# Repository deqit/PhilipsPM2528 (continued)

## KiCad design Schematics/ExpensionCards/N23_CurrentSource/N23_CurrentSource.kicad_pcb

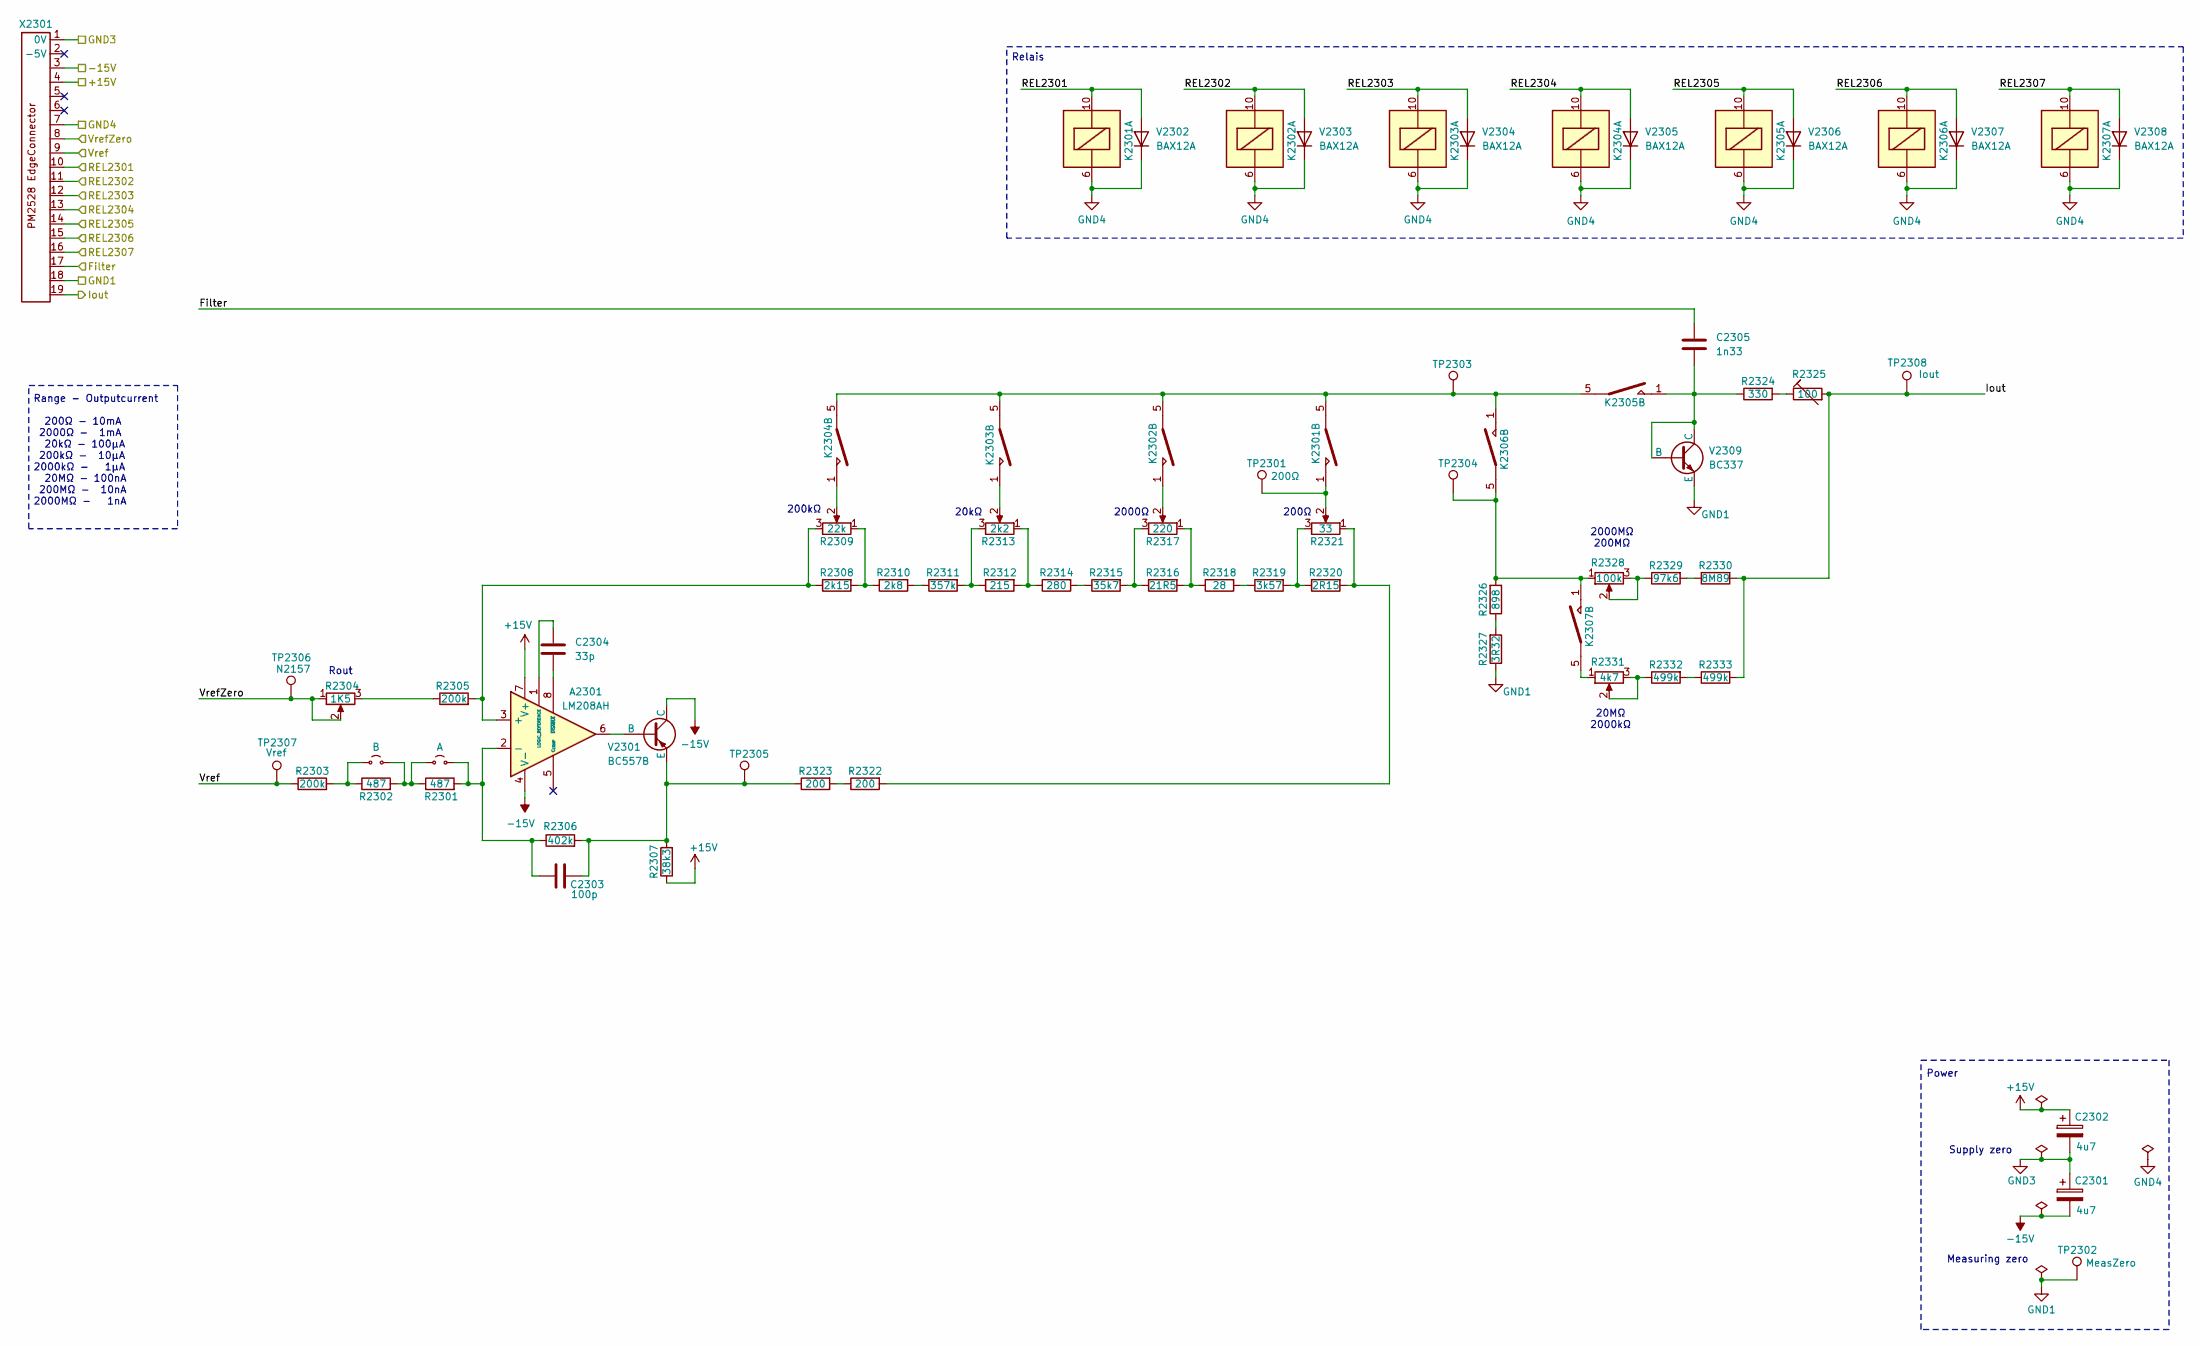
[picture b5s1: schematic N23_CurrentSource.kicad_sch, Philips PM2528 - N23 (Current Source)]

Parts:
A2301: LM208AH; TO-99-8
C2301, C2302: 4u7; CP_Radial_Tantal_D4.5mm_P5.00mm
C2303: 100p; C_Disc_D4.3mm_W1.9mm_P5.00mm
C2304: 33p; C_Disc_D4.3mm_W1.9mm_P5.00mm
C2305: 1n33; C_Axial_L5.1mm_D3.1mm_P15.00mm_Horizontal
JP2301: B; TestPoint_Bridge_Pitch5.08mm_Drill0.7mm
JP2302: A; TestPoint_Bridge_Pitch5.08mm_Drill0.7mm
K2301, K2302, K2303, K2304, K2305, K2306, K2307: Reed relay assy
R2301: 487; R_Axial_DIN0309_L9.0mm_D3.2mm_P12.70mm_Horizontal
R2302: 487; R_Axial_DIN0207_L6.3mm_D2.5mm_P10.16mm_Horizontal
R2303: 200k; R_Axial_DIN0207_L6.3mm_D2.5mm_P10.16mm_Horizontal
R2304: 1K5; Trimmer vertical
R2305: 200k; R_Axial_DIN0309_L9.0mm_D3.2mm_P12.70mm_Horizontal
R2306: 402k; R_Axial_DIN0309_L9.0mm_D3.2mm_P12.70mm_Horizontal
R2307: 38k3; R_Axial_DIN0207_L6.3mm_D2.5mm_P10.16mm_Horizontal
R2308: 2k15; R_Axial_DIN0207_L6.3mm_D2.5mm_P10.16mm_Horizontal
R2309: 22k; Trimmer vertical
R2310: 2k8; R_Axial_DIN0207_L6.3mm_D2.5mm_P10.16mm_Horizontal
R2311: 357k; R_Axial_DIN0309_L9.0mm_D3.2mm_P12.70mm_Horizontal
R2312: 215; R_Axial_DIN0207_L6.3mm_D2.5mm_P10.16mm_Horizontal
R2313: 2k2; Trimmer vertical
R2314: 280; R_Axial_DIN0207_L6.3mm_D2.5mm_P10.16mm_Horizontal
R2315: 35k7; R_Axial_DIN0207_L6.3mm_D2.5mm_P10.16mm_Horizontal
R2316: 21R5; R_Axial_DIN0207_L6.3mm_D2.5mm_P10.16mm_Horizontal
R2317: 220; Trimmer vertical
R2318: 28; R_Axial_DIN0207_L6.3mm_D2.5mm_P10.16mm_Horizontal
R2319: 3k57; R_Axial_DIN0207_L6.3mm_D2.5mm_P10.16mm_Horizontal
R2320: 2R15; R_Axial_DIN0207_L6.3mm_D2.5mm_P10.16mm_Horizontal
R2321: 33; Trimmer vertical
R2322, R2323: 200; R_Axial_DIN0309_L9.0mm_D3.2mm_P12.70mm_Horizontal
R2324: 330; R_Axial_DIN0614_L14.3mm_D5.7mm_P25.40mm_Horizontal
R2325: 100; RV_Disc_D7mm_W3.9mm_P5mm
R2326: 898; R_Axial_DIN0207_L6.3mm_D2.5mm_P10.16mm_Horizontal
R2327: 3R32; R_Axial_DIN0207_L6.3mm_D2.5mm_P10.16mm_Horizontal
R2328: 100k; Trimmer vertical
R2329: 97k6; R_Axial_DIN0207_L6.3mm_D2.5mm_P10.16mm_Horizontal
R2330: 8M89; R_Axial_DIN0411_L9.9mm_D3.6mm_P15.24mm_Horizontal
R2331: 4k7; Trimmer vertical
R2332, R2333: 499k; R_Axial_DIN0309_L9.0mm_D3.2mm_P12.70mm_Horizontal
TP2301: 200Ω; Pin_D0.9mm_L10.0mm_W2.4mm_FlatFork
TP2302: MeasZero; Pin_D0.9mm_L10.0mm_W2.4mm_FlatFork
TP2303, TP2304, TP2305: Pin_D0.9mm_L10.0mm_W2.4mm_FlatFork
TP2306: N2157; Pin_D0.9mm_L10.0mm_W2.4mm_FlatFork
TP2307: Vref; Pin_D0.9mm_L10.0mm_W2.4mm_FlatFork
TP2308: Iout; Pin_D0.9mm_L10.0mm_W2.4mm_FlatFork
V2301: BC557B; TO-92
V2302, V2303, V2304, V2305, V2306, V2307, V2308: BAX12A; D_DO-41_SOD81_P10.16mm_Horizontal
V2309: BC337; TO-92
X2301: PM2528_RiserCardConnector

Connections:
+15V: A2301.7 (V+), C2302.1, R2307.1, X2301.4
-15V: A2301.4 (V-), C2301.2, V2301.1 (C), X2301.3
/Filter: C2305.2, X2301.17
/Iout: R2325.2, R2330.2, R2333.2, TP2308.1, X2301.19
/REL2301: K2301.10, V2302.2 (A), X2301.10
/REL2302: K2302.10, V2303.2 (A), X2301.11
/REL2303: K2303.10, V2304.2 (A), X2301.12
/REL2304: K2304.10, V2305.2 (A), X2301.13
/REL2305: K2305.10, V2306.2 (A), X2301.14
/REL2306: K2306.10, V2307.2 (A), X2301.15
/REL2307: K2307.10, V2308.2 (A), X2301.16
/Vref: R2303.1, TP2307.1, X2301.9
/VrefZero: R2304.1, R2304.2, TP2306.1, X2301.8
GND1: R2327.1, TP2302.1, V2309.3 (E), X2301.18
GND3: C2301.1, C2302.2, X2301.1 (0V)
GND4: K2301.6, K2302.6, K2303.6, K2304.6, K2305.6, K2306.6, K2307.6, V2302.1 (K), V2303.1 (K), V2304.1 (K), V2305.1 (K), V2306.1 (K), V2307.1 (K), V2308.1 (K), X2301.7
unnamed: A2301.3 (+), R2305.2, R2308.1, R2309.3
unnamed: A2301.2 (-), C2303.2, JP2302.2 (B), R2301.2, R2306.1
unnamed: A2301.1 (LOGIC_REFERENCE), C2304.1
unnamed: A2301.8 (~DISABLE), C2304.2
unnamed: JP2301.1 (A), R2302.1, R2303.2
unnamed: JP2301.2 (B), JP2302.1 (A), R2301.1, R2302.2
unnamed: K2301.1, R2321.2, TP2301.1
unnamed: K2301.5, K2302.5, K2303.5, K2304.5, K2305.5, K2306.1, TP2303.1
unnamed: K2302.1, R2317.2
unnamed: K2303.1, R2313.2
unnamed: K2304.1, R2309.2
unnamed: K2306.5, K2307.1, R2326.2, R2328.1, TP2304.1
unnamed: K2307.5, R2331.1
unnamed: R2304.3, R2305.1
unnamed: R2308.2, R2309.1, R2310.1
unnamed: R2310.2, R2311.1
unnamed: R2311.2, R2312.1, R2313.3
unnamed: R2312.2, R2313.1, R2314.1
unnamed: R2314.2, R2315.1
unnamed: R2315.2, R2316.1, R2317.3
unnamed: R2316.2, R2317.1, R2318.1
unnamed: R2318.2, R2319.1
unnamed: R2319.2, R2320.1, R2321.3
unnamed: R2320.2, R2321.1, R2322.2
unnamed: R2322.1, R2323.2
unnamed: R2324.2, R2325.1
unnamed: R2326.1, R2327.2
unnamed: R2328.2, R2328.3, R2329.1
unnamed: R2329.2, R2330.1
unnamed: R2331.2, R2331.3, R2332.1
unnamed: R2332.2, R2333.1
unnamed: A2301.6, V2301.2 (B)
unnamed: C2303.1, R2306.2, R2307.2, R2323.1, TP2305.1, V2301.3 (E)
unnamed: C2305.1, K2305.1, R2324.1, V2309.1 (C), V2309.2 (B)

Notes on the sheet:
200Ω
Power
Measuring zero
20kΩ
2000MΩ 200MΩ
200kΩ
20MΩ 2000kΩ
Relais
2000Ω
Rout
Range - Outputcurrent 200Ω - 10mA 2000Ω - 1mA 20kΩ - 100µA 200kΩ - 10µA 2000kΩ - 1µA 20MΩ - 100nA 200MΩ - 10nA 2000MΩ - 1nA
Supply zero

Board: 2 copper layers, 66 parts (0 on the bottom side), 50 nets, no tracks yet.

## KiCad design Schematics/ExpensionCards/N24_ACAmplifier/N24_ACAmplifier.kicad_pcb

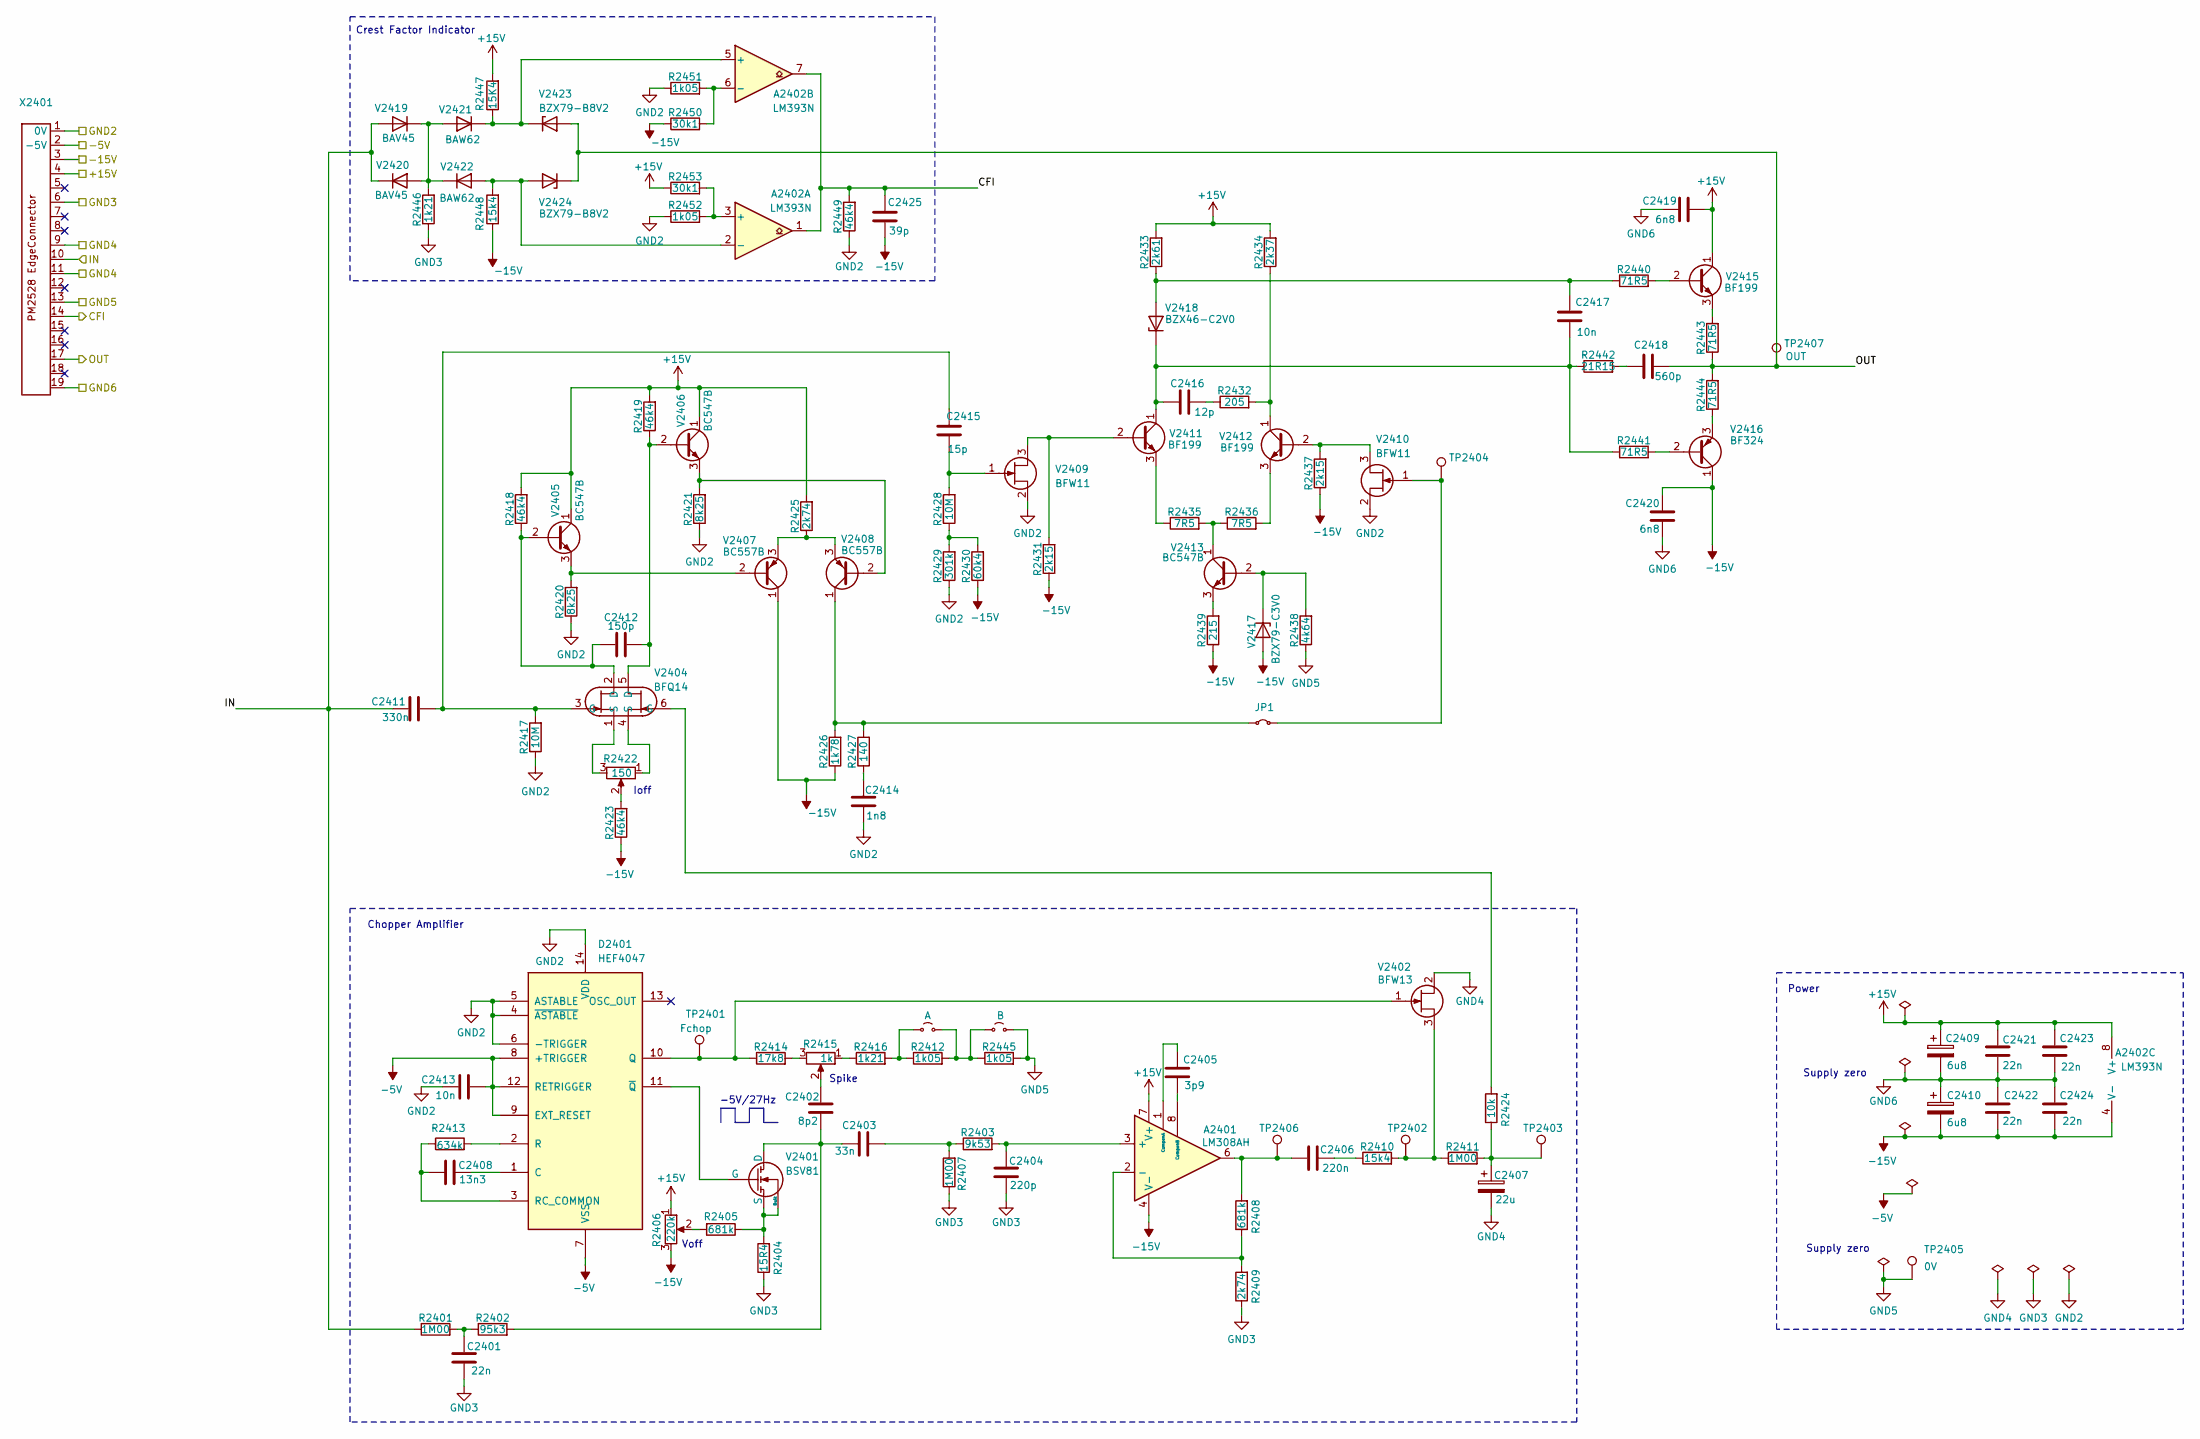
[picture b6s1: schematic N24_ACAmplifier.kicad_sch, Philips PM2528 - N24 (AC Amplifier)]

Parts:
A2401: LM308AH; DIP-8_W7.62mm
A2402: LM393N; DIP-8_W7.62mm
C2401: 22n; C_Rect_L13.0mm_W4.0mm_P10.00mm_FKS3_FKP3_MKS4
C2402: 8p2; C_Disc_D4.3mm_W1.9mm_P5.00mm
C2403: 33n; C_Rect_L13.0mm_W4.0mm_P10.00mm_FKS3_FKP3_MKS4
C2404: 220p; C_Disc_D4.3mm_W1.9mm_P5.00mm
C2405: 3p9; C_Disc_D4.3mm_W1.9mm_P5.00mm
C2406: 220n; C_Rect_L13.0mm_W4.0mm_P10.00mm_FKS3_FKP3_MKS4
C2407: 22u; CP_Radial_Tantal_D4.5mm_P5.00mm
C2408: 13n3; C_Axial_L5.1mm_D3.1mm_P15.00mm_Horizontal
C2409, C2410: 6u8; CP_Radial_Tantal_D4.5mm_P5.00mm
C2411: 330n; C_Rect_L18.0mm_W5.0mm_P15.00mm_FKS3_FKP3
C2412: 150p; C_Disc_D4.3mm_W1.9mm_P5.00mm
C2413, C2417: 10n; C_Disc_D4.3mm_W1.9mm_P5.00mm
C2414: 1n8; C_Disc_D4.3mm_W1.9mm_P5.00mm
C2415: 15p; C_Disc_D4.3mm_W1.9mm_P5.00mm
C2416: 12p; C_Disc_D4.3mm_W1.9mm_P5.00mm
C2418: 560p; C_Disc_D4.3mm_W1.9mm_P5.00mm
C2419, C2420: 6n8; C_Disc_D4.3mm_W1.9mm_P5.00mm
C2421, C2422, C2423, C2424: 22n; C_Disc_D4.3mm_W1.9mm_P5.00mm
C2425: 39p; C_Disc_D4.3mm_W1.9mm_P5.00mm
D2401: HEF4047; DIP-14_W7.62mm
JP1: Jumper_2_Small_Bridged; TestPoint_Bridge_Pitch5.08mm_Drill0.7mm
JP2401: A; TestPoint_Bridge_Pitch5.08mm_Drill0.7mm
JP2402: B; TestPoint_Bridge_Pitch5.08mm_Drill0.7mm
R2401, R2407, R2411: 1M00; R_Axial_DIN0207_L6.3mm_D2.5mm_P10.16mm_Horizontal
R2402: 95k3; R_Axial_DIN0207_L6.3mm_D2.5mm_P10.16mm_Horizontal
R2403: 9k53; R_Axial_DIN0207_L6.3mm_D2.5mm_P10.16mm_Horizontal
R2404: 15R4; R_Axial_DIN0207_L6.3mm_D2.5mm_P10.16mm_Horizontal
R2405, R2408: 681k; R_Axial_DIN0207_L6.3mm_D2.5mm_P10.16mm_Horizontal
R2406: 220k; Trimmer vertical
R2409, R2425: 2k74; R_Axial_DIN0207_L6.3mm_D2.5mm_P10.16mm_Horizontal
R2410, R2448: 15k4; R_Axial_DIN0207_L6.3mm_D2.5mm_P10.16mm_Horizontal
R2412, R2445, R2451, R2452: 1k05; R_Axial_DIN0207_L6.3mm_D2.5mm_P10.16mm_Horizontal
R2413: 634k; R_Axial_DIN0207_L6.3mm_D2.5mm_P10.16mm_Horizontal
R2414: 17k8; R_Axial_DIN0207_L6.3mm_D2.5mm_P10.16mm_Horizontal
R2415: 1k; Trimmer vertical
R2416, R2446: 1k21; R_Axial_DIN0207_L6.3mm_D2.5mm_P10.16mm_Horizontal
R2417, R2428: 10M; R_Axial_DIN0207_L6.3mm_D2.5mm_P10.16mm_Horizontal
R2418, R2419, R2423, R2449: 46k4; R_Axial_DIN0207_L6.3mm_D2.5mm_P10.16mm_Horizontal
R2420, R2421: 8k25; R_Axial_DIN0207_L6.3mm_D2.5mm_P10.16mm_Horizontal
R2422: 150; Trimmer vertical
R2424: 10k; R_Axial_DIN0207_L6.3mm_D2.5mm_P10.16mm_Horizontal
R2426: 1k78; R_Axial_DIN0207_L6.3mm_D2.5mm_P10.16mm_Horizontal
R2427: 140; R_Axial_DIN0207_L6.3mm_D2.5mm_P10.16mm_Horizontal
R2429: 301k; R_Axial_DIN0207_L6.3mm_D2.5mm_P10.16mm_Horizontal
R2430: 60k4; R_Axial_DIN0207_L6.3mm_D2.5mm_P10.16mm_Horizontal
R2431, R2437: 2k15; R_Axial_DIN0207_L6.3mm_D2.5mm_P10.16mm_Horizontal
R2432: 205; R_Axial_DIN0207_L6.3mm_D2.5mm_P10.16mm_Horizontal
R2433: 2k61; R_Axial_DIN0207_L6.3mm_D2.5mm_P10.16mm_Horizontal
R2434: 2k37; R_Axial_DIN0207_L6.3mm_D2.5mm_P10.16mm_Horizontal
R2435, R2436: 7R5; R_Axial_DIN0207_L6.3mm_D2.5mm_P10.16mm_Horizontal
R2438: 4k64; R_Axial_DIN0207_L6.3mm_D2.5mm_P10.16mm_Horizontal
R2439: 215; R_Axial_DIN0207_L6.3mm_D2.5mm_P10.16mm_Horizontal
R2440, R2441, R2443, R2444: 71R5; R_Axial_DIN0207_L6.3mm_D2.5mm_P10.16mm_Horizontal
R2442: 21R15; R_Axial_DIN0207_L6.3mm_D2.5mm_P10.16mm_Horizontal
R2447: 15K4; R_Axial_DIN0207_L6.3mm_D2.5mm_P10.16mm_Horizontal
R2450, R2453: 30k1; R_Axial_DIN0207_L6.3mm_D2.5mm_P10.16mm_Horizontal
TP2401: Fchop; Pin_D0.9mm_L10.0mm_W2.4mm_FlatFork
TP2402, TP2403: Pin_D0.9mm_L10.0mm_W2.4mm_FlatFork
TP2404: something; Pin_D0.9mm_L10.0mm_W2.4mm_FlatFork
TP2405: 0V; Pin_D0.9mm_L10.0mm_W2.4mm_FlatFork
TP2406: AC_RMS?; Pin_D0.9mm_L10.0mm_W2.4mm_FlatFork
TP2407: OUT; Pin_D0.9mm_L10.0mm_W2.4mm_FlatFork
V2401: BSV81; TO-72-4
V2402: BFW13; TO-72-4
V2404: BFQ14; TO-75-6
V2405, V2406, V2413: BC547B; TO-92_Inline
V2407, V2408: BC557B; TO-92_Inline
V2409, V2410: BFW11; TO-72-4
V2411, V2412, V2415: BF199; TO-92_Inline
V2416: BF324; TO-92_Inline
V2417: BZX79-C3V0; D_DO-35_SOD27_P10.16mm_Horizontal
V2418: BZX46-C2V0; D_DO-35_SOD27_P10.16mm_Horizontal
V2419, V2420: BAV45; TO-72-4
V2421, V2422: BAW62; D_DO-35_SOD27_P10.16mm_Horizontal
V2423, V2424: BZX79-B8V2; D_DO-35_SOD27_P10.16mm_Horizontal
X2401: PM2528_RiserCardConnector

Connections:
+15V: A2401.7 (V+), A2402.8 (V+), C2409.1, C2419.2, C2421.1, C2423.1, R2406.1, R2418.2, R2419.2, R2425.2, R2433.2, R2434.2, R2447.2, R2453.1, V2405.1 (C), V2406.1 (C), V2415.1 (C), X2401.4
-5V: C2413.1, D2401.7 (VSS), D2401.8 (+TRIGGER), D2401.9 (EXT_RESET), D2401.12 (RETRIGGER), X2401.2 (-5V)
-15V: A2401.4 (V-), A2402.4 (V-), C2410.2, C2420.1, C2422.2, C2424.2, C2425.1, R2406.3, R2423.1, R2426.1, R2430.1, R2431.1, R2437.1, R2439.1, R2448.1, R2450.1, V2407.1 (C), V2416.1 (C), V2417.2 (A), X2401.3
/CFI: A2402.1, A2402.7, C2425.2, R2449.2, X2401.14
/IN: C2411.2, R2401.1, V2419.2 (A), V2420.1 (K), X2401.10
/OUT: C2418.1, R2443.1, R2444.2, TP2407.1, V2423.2 (A), V2424.1 (K), X2401.17
GND2: C2413.2, C2414.1, D2401.4 (~ASTABLE), D2401.5 (ASTABLE), D2401.6 (-TRIGGER), D2401.14 (VDD), R2417.1, R2420.1, R2421.1, R2429.1, R2449.1, R2451.1, R2452.1, V2409.2 (S), V2410.2 (S), X2401.1 (0V)
GND3: C2401.2, C2404.2, R2404.1, R2407.1, R2409.1, R2446.1, X2401.6
GND4: C2407.2, V2402.2 (S), X2401.9, X2401.11
GND5: JP2402.2 (B), R2438.1, R2445.2, TP2405.1, X2401.13
GND6: C2409.2, C2410.1, C2419.1, C2420.2, C2421.2, C2422.1, C2423.2, C2424.1, X2401.19
unnamed: A2401.3 (+), C2404.1, R2403.2
unnamed: A2401.2 (-), R2408.1, R2409.2
unnamed: A2401.1 (CompenA), C2405.1
unnamed: A2401.8 (CompenB), C2405.2
unnamed: A2401.6, C2406.1, R2408.2, TP2406.1
unnamed: A2402.3 (+), R2452.2, R2453.2
unnamed: A2402.2 (-), R2448.2, V2422.2 (A), V2424.2 (A)
unnamed: A2402.5 (+), R2447.1, V2421.1 (K), V2423.1 (K)
unnamed: A2402.6 (-), R2450.2, R2451.2
unnamed: C2401.1, R2401.2, R2402.1
unnamed: C2402.1, R2415.2
unnamed: C2403.2, R2403.1, R2407.2
unnamed: C2406.2, R2410.1
unnamed: C2407.1, R2411.2, R2424.1, TP2403.1
unnamed: C2411.1, C2415.1, R2417.2, V2404.3 (G)
unnamed: C2414.2, R2427.1
unnamed: C2416.1, R2432.1
unnamed: C2418.2, R2442.2
unnamed: C2408.1, D2401.1 (C)
unnamed: D2401.10 (Q), R2414.1, TP2401.1, V2402.1 (G)
unnamed: D2401.2 (R), R2413.2
unnamed: C2408.2, D2401.3 (RC_COMMON), R2413.1
unnamed: D2401.11 (~Q), V2401.2 (G)
unnamed: JP1.1 (A), R2426.2, R2427.2, V2408.1 (C)
unnamed: JP1.2 (B), TP2404.1, V2410.1 (G)
unnamed: JP2401.1 (A), R2412.1, R2416.2
unnamed: JP2401.2 (B), JP2402.1 (A), R2412.2, R2445.1
unnamed: R2405.2, R2406.2
unnamed: R2414.2, R2415.3
unnamed: R2415.1, R2416.1
unnamed: R2422.1, V2404.4 (S)
unnamed: R2422.2, R2423.2
unnamed: R2422.3, V2404.1 (S)
unnamed: R2424.2, V2404.6 (G)
unnamed: R2428.1, R2429.2, R2430.2
unnamed: R2404.2, R2405.1, V2401.3 (S), V2401.4 (Bulk)
unnamed: C2402.2, C2403.1, R2402.2, V2401.1 (D)
unnamed: R2410.2, R2411.1, TP2402.1, V2402.3 (D)
unnamed: C2412.2, R2418.1, V2404.2 (D), V2405.2 (B)
unnamed: R2420.2, V2405.3 (E), V2407.2 (B)
unnamed: C2412.1, R2419.1, V2404.5 (D), V2406.2 (B)
unnamed: R2421.2, V2406.3 (E), V2408.2 (B)
unnamed: R2425.1, V2407.3 (E), V2408.3 (E)
unnamed: R2431.2, V2409.3 (D), V2411.2 (B)
unnamed: C2415.2, R2428.2, V2409.1 (G)
unnamed: R2437.2, V2410.3 (D), V2412.2 (B)
unnamed: C2416.2, C2417.1, R2441.1, R2442.1, V2411.1 (C), V2418.1 (K)
unnamed: R2435.1, V2411.3 (E)
unnamed: R2432.2, R2434.1, V2412.1 (C)
unnamed: R2436.2, V2412.3 (E)
unnamed: R2438.2, V2413.2 (B), V2417.1 (K)
unnamed: R2435.2, R2436.1, V2413.1 (C)
unnamed: R2439.2, V2413.3 (E)
unnamed: R2440.2, V2415.2 (B)
unnamed: R2443.2, V2415.3 (E)
unnamed: R2441.2, V2416.2 (B)
unnamed: R2444.1, V2416.3 (E)
unnamed: C2417.2, R2433.1, R2440.1, V2418.2 (A)
unnamed: R2446.2, V2419.1 (K), V2420.2 (A), V2421.2 (A), V2422.1 (K)

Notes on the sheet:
Power
-5V/27Hz
Voff
Supply zero
Ioff
Spike
Chopper Amplifier
Crest Factor Indicator

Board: 2 copper layers, 114 parts (0 on the bottom side), 70 nets, no tracks yet.

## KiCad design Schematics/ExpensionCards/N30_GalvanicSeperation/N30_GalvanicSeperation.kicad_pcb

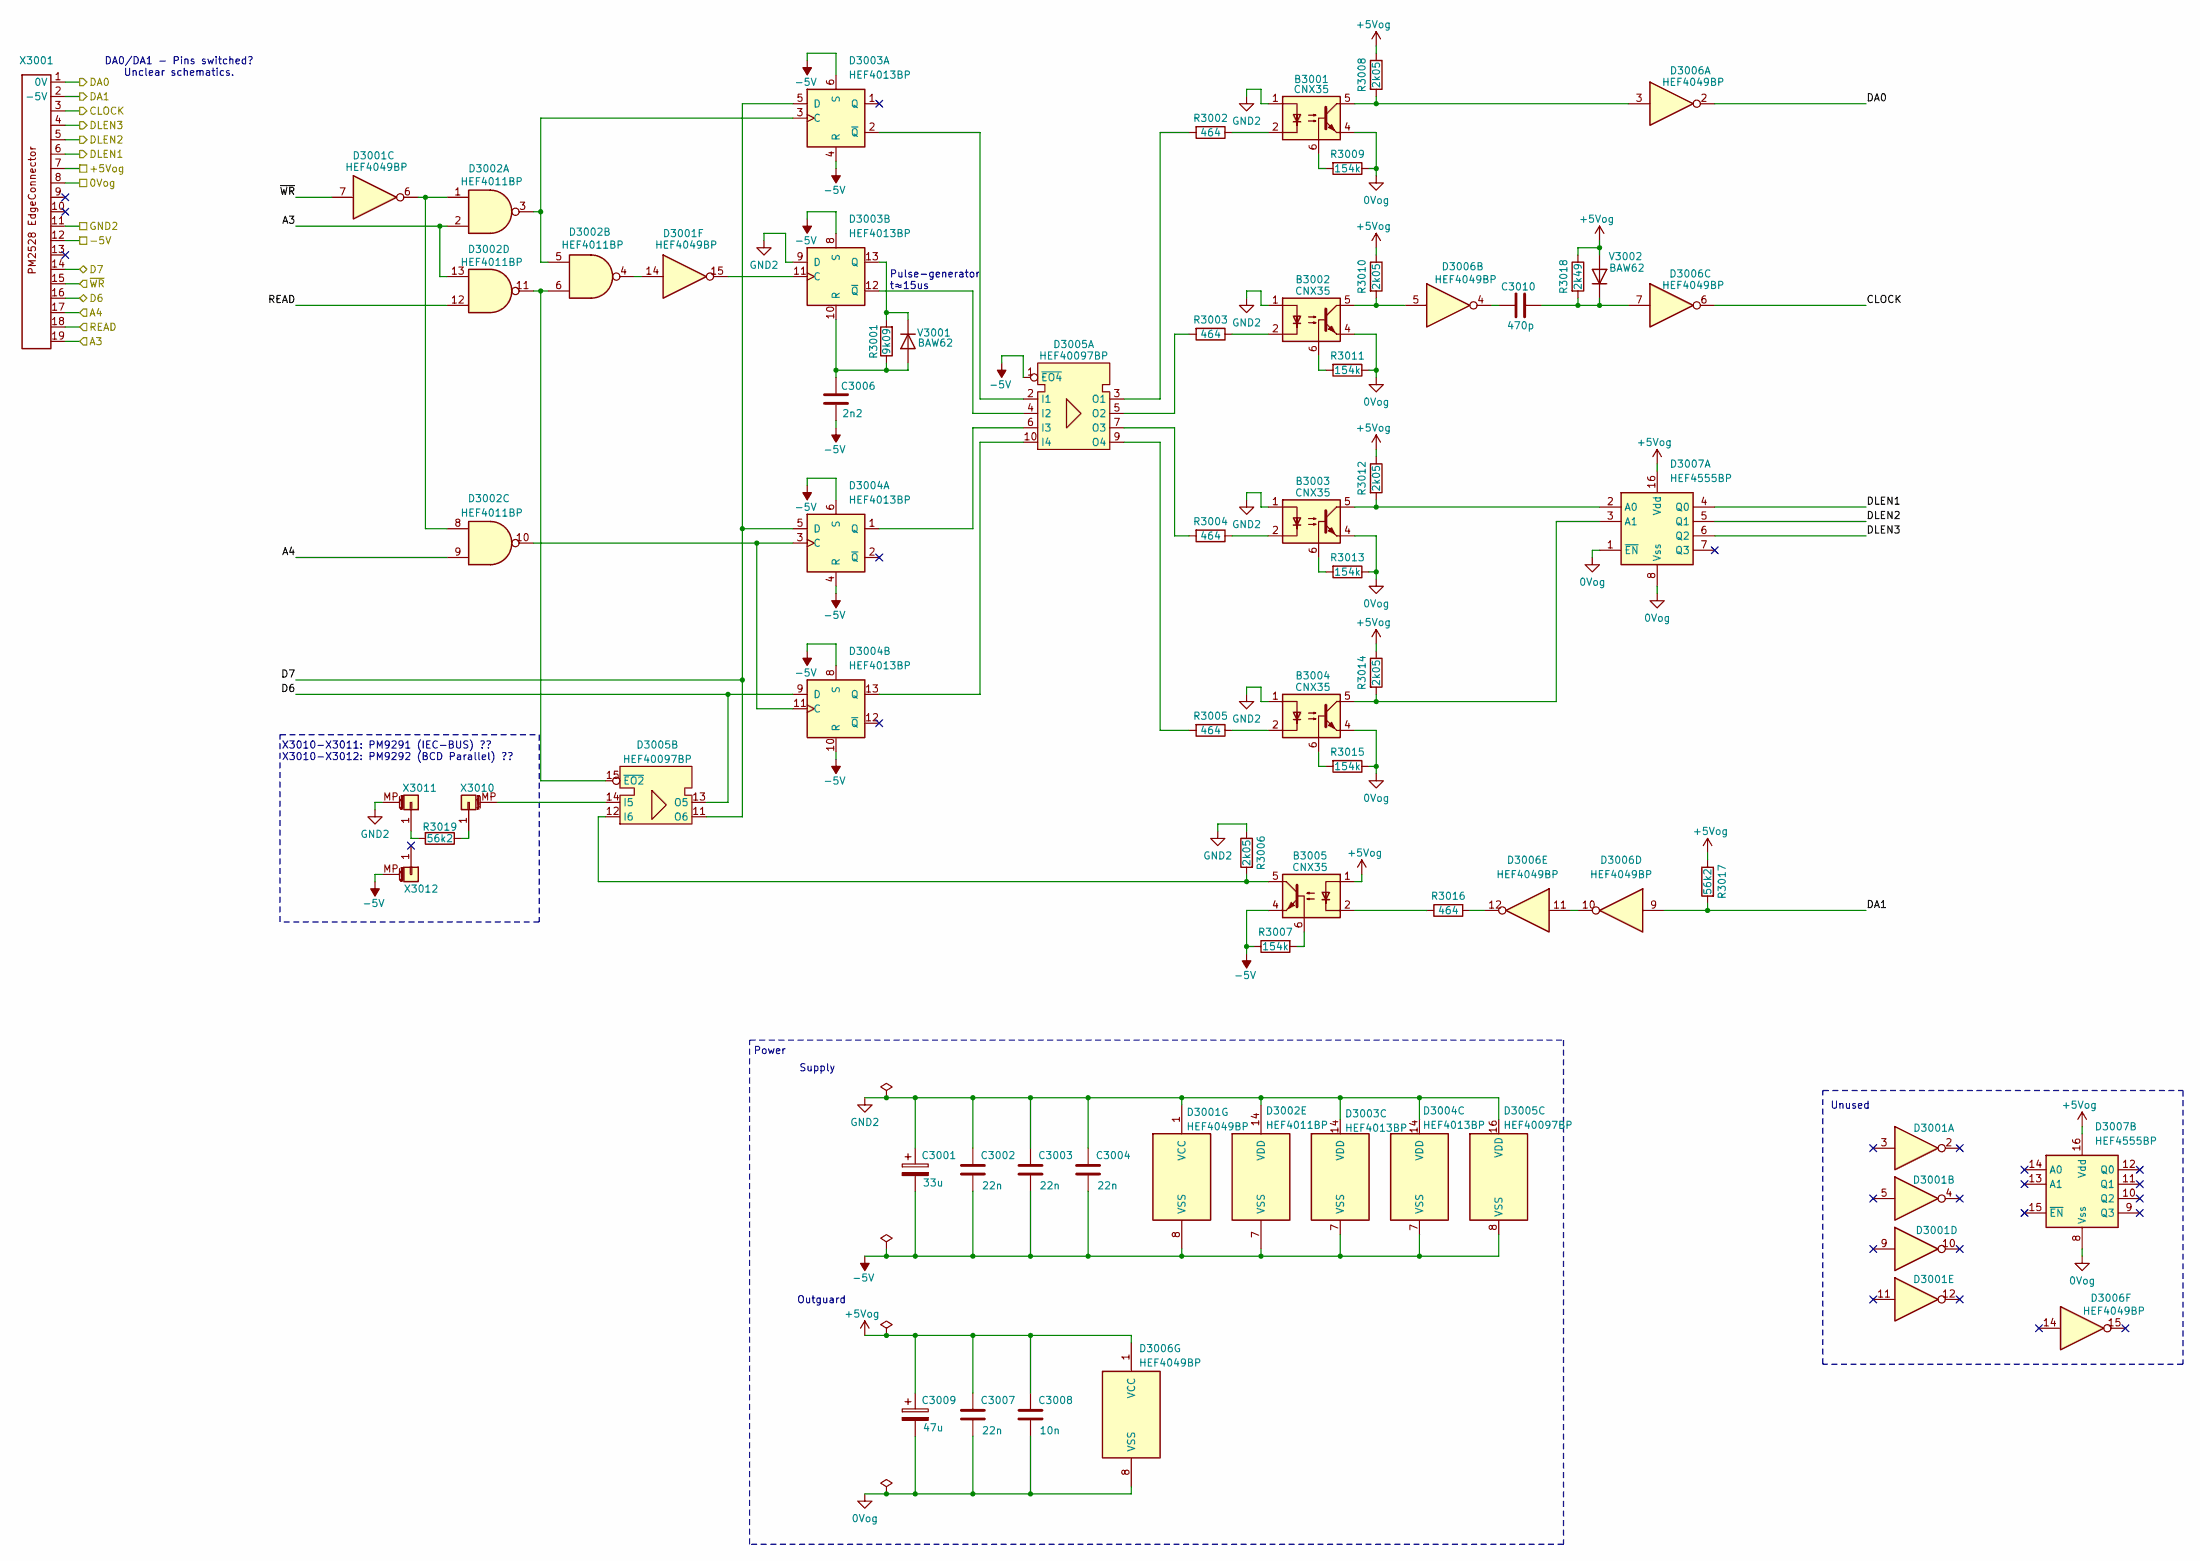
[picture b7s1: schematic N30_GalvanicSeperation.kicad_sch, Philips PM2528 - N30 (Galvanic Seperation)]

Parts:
B3001, B3002, B3003, B3004, B3005: CNX35; DIP-6_W7.62mm
C3001: 33u; CP_Radial_Tantal_D7.0mm_P5.00mm
C3002, C3003, C3004, C3007: 22n; C_Axial_L5.1mm_D3.1mm_P10.00mm_Horizontal
C3006: 2n2; C_Axial_L5.1mm_D3.1mm_P10.00mm_Horizontal
C3008: 10n; C_Axial_L5.1mm_D3.1mm_P10.00mm_Horizontal
C3009: 47u; CP_Axial_L10.0mm_D6.0mm_P15.00mm_Horizontal
C3010: 470p; C_Axial_L5.1mm_D3.1mm_P10.00mm_Horizontal
D3001, D3006: HEF4049BP; DIP-16_W7.62mm
D3002: HEF4011BP; DIP-14_W7.62mm
D3003, D3004: HEF4013BP; DIP-14_W7.62mm
D3005: HEF40097BP; DIP-16_W7.62mm
D3007: HEF4555BP; DIP-16_W7.62mm
R3001: 9k09; R_Axial_DIN0207_L6.3mm_D2.5mm_P10.16mm_Horizontal
R3002, R3003, R3004, R3005, R3016: 464; R_Axial_DIN0207_L6.3mm_D2.5mm_P10.16mm_Horizontal
R3006, R3008, R3010, R3012, R3014: 2k05; R_Axial_DIN0207_L6.3mm_D2.5mm_P10.16mm_Horizontal
R3007, R3009, R3011, R3013, R3015: 154k; R_Axial_DIN0207_L6.3mm_D2.5mm_P10.16mm_Horizontal
R3017, R3019: 56k2; R_Axial_DIN0207_L6.3mm_D2.5mm_P10.16mm_Horizontal
R3018: 2k49; R_Axial_DIN0207_L6.3mm_D2.5mm_P10.16mm_Horizontal
V3001, V3002: BAW62; D_DO-35_SOD27_P7.62mm_Horizontal
X3001: PM2528_RiserCardConnector
X3010, X3011, X3012: Conn_01x01_MountingPin; Pin_D1.1mm_L8.5mm_W2.5mm_FlatFork

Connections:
0Vog: B3001.4, B3002.4, B3003.4, B3004.4, C3007.2, C3008.2, C3009.2, D3006.8 (VSS), D3007.1 (~EN), D3007.8 (Vss), R3009.1, R3011.1, R3013.1, R3015.1, X3001.8
+5Vog: B3005.1, C3007.1, C3008.1, C3009.1, D3006.1 (VCC), D3007.16 (Vdd), R3008.1, R3010.1, R3012.1, R3014.1, R3017.1, R3018.1, V3002.2 (A), X3001.7
-5V: B3005.4, C3001.2, C3002.2, C3003.2, C3004.2, C3006.2, D3001.8 (VSS), D3002.7 (VSS), D3003.4 (R), D3003.6 (S), D3003.7 (VSS), D3003.8 (S), D3004.4 (R), D3004.6 (S), D3004.7 (VSS), D3004.8 (S), D3004.10 (R), D3005.1 (~EO4), D3005.8 (VSS), R3007.1, X3001.12, X3012.MP (MountPin)
/A3: D3002.2, D3002.13, X3001.19
/A4: D3002.9, X3001.17
/CLOCK: D3006.6, X3001.3
/D6: D3004.9 (D), D3005.13 (O5), X3001.16
/D7: D3003.5 (D), D3004.5 (D), D3005.11 (O6), X3001.14
/DA0: D3006.2, X3001.1 (0V)
/DA1: D3006.9, R3017.2, X3001.2 (-5V)
/DLEN1: D3007.4 (Q0), X3001.6
/DLEN2: D3007.5 (Q1), X3001.5
/DLEN3: D3007.6 (Q2), X3001.4
/READ: D3002.12, X3001.18
/~WR: D3001.7, X3001.15
GND2: B3001.1, B3002.1, B3003.1, B3004.1, C3001.1, C3002.1, C3003.1, C3004.1, D3001.1 (VCC), D3002.14 (VDD), D3003.9 (D), D3003.14 (VDD), D3004.14 (VDD), D3005.16 (VDD), R3006.1, X3001.11, X3011.MP (MountPin)
unnamed: B3001.2, R3002.1
unnamed: B3001.5, D3006.3, R3008.2
unnamed: B3001.6, R3009.2
unnamed: B3002.2, R3003.1
unnamed: B3002.5, D3006.5, R3010.2
unnamed: B3002.6, R3011.2
unnamed: B3003.2, R3004.1
unnamed: B3003.6, R3013.2
unnamed: B3004.2, R3005.1
unnamed: B3004.6, R3015.2
unnamed: B3005.2, R3016.1
unnamed: B3005.6, R3007.2
unnamed: C3010.1, D3006.4
unnamed: D3001.6, D3002.1, D3002.8
unnamed: D3001.14, D3002.4
unnamed: D3002.3, D3002.5, D3003.3 (C)
unnamed: D3003.2 (~Q), D3005.2 (I1)
unnamed: D3001.15, D3003.11 (C)
unnamed: D3003.13 (Q), R3001.2, V3001.1 (K)
unnamed: C3006.1, D3003.10 (R), R3001.1, V3001.2 (A)
unnamed: D3003.12 (~Q), D3005.4 (I2)
unnamed: D3002.10, D3004.3 (C), D3004.11 (C)
unnamed: D3004.1 (Q), D3005.6 (I3)
unnamed: D3004.13 (Q), D3005.10 (I4)
unnamed: D3005.3 (O1), R3002.2
unnamed: D3005.5 (O2), R3003.2
unnamed: D3005.7 (O3), R3004.2
unnamed: D3005.9 (O4), R3005.2
unnamed: D3005.14 (I5), X3010.MP (MountPin)
unnamed: B3005.5, D3005.12 (I6), R3006.2
unnamed: D3002.6, D3002.11, D3005.15 (~EO2)
unnamed: D3006.10, D3006.11
unnamed: D3006.12, R3016.2
unnamed: B3003.5, D3007.2 (A0), R3012.2
unnamed: B3004.5, D3007.3 (A1), R3014.2
unnamed: C3010.2, D3006.7, R3018.2, V3002.1 (K)
unnamed: R3019.1, X3010.1
unnamed: R3019.2, X3011.1

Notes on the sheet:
Unused
Outguard
Supply
Pulse-generator t≈15us
X3010-X3011: PM9291 (IEC-BUS) ?? X3010-X3012: PM9292 (BCD Parallel) ??
DA0/DA1 - Pins switched? Unclear schematics.
Power

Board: 2 copper layers, 46 parts (0 on the bottom side), 53 nets, no tracks yet.
